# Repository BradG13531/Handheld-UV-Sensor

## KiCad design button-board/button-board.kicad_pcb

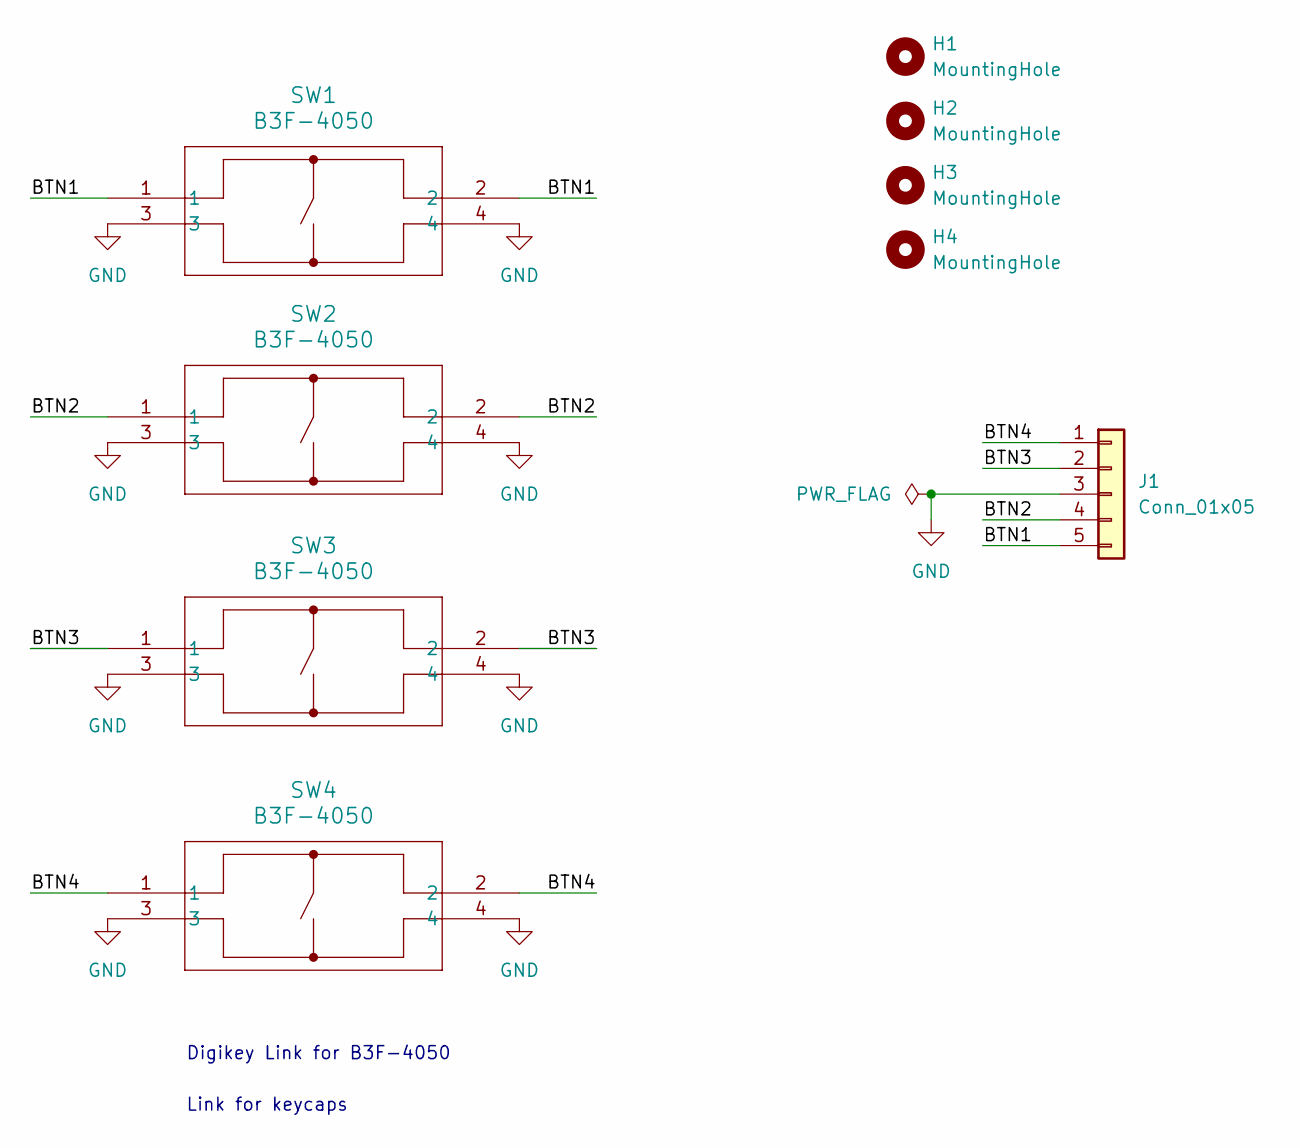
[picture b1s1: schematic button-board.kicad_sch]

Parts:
H1, H2, H3, H4: MountingHole; MountingHole_2.2mm_M2
J1: Conn_01x05; JST_PH_S5B-PH-K_1x05_P2.00mm_Horizontal
SW1, SW2, SW3, SW4: B3F-4050; SW_B3F-4050_OMR

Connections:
/BTN1: J1.5, SW1.1, SW1.2
/BTN2: J1.4, SW2.1, SW2.2
/BTN3: J1.2, SW3.1, SW3.2
/BTN4: J1.1, SW4.1, SW4.2
GND: J1.3, SW1.3, SW1.4, SW2.3, SW2.4, SW3.3, SW3.4, SW4.3, SW4.4

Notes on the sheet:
Digikey Link for B3F-4050
Link for keycaps

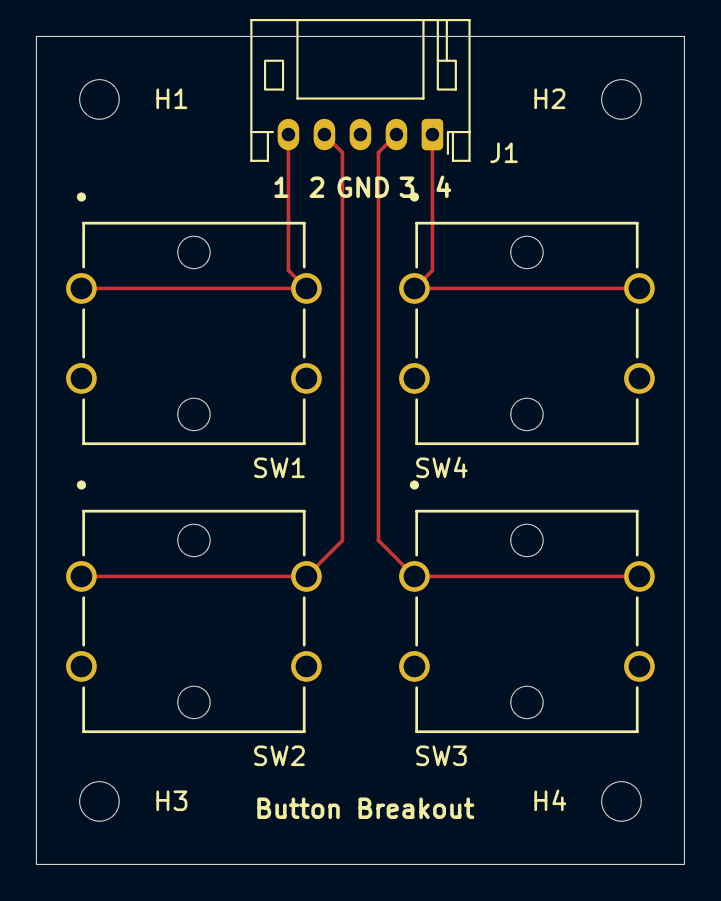
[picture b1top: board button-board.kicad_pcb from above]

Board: 2 copper layers, 36.0 x 46.0 mm, 9 parts (0 on the bottom side), 5 nets.

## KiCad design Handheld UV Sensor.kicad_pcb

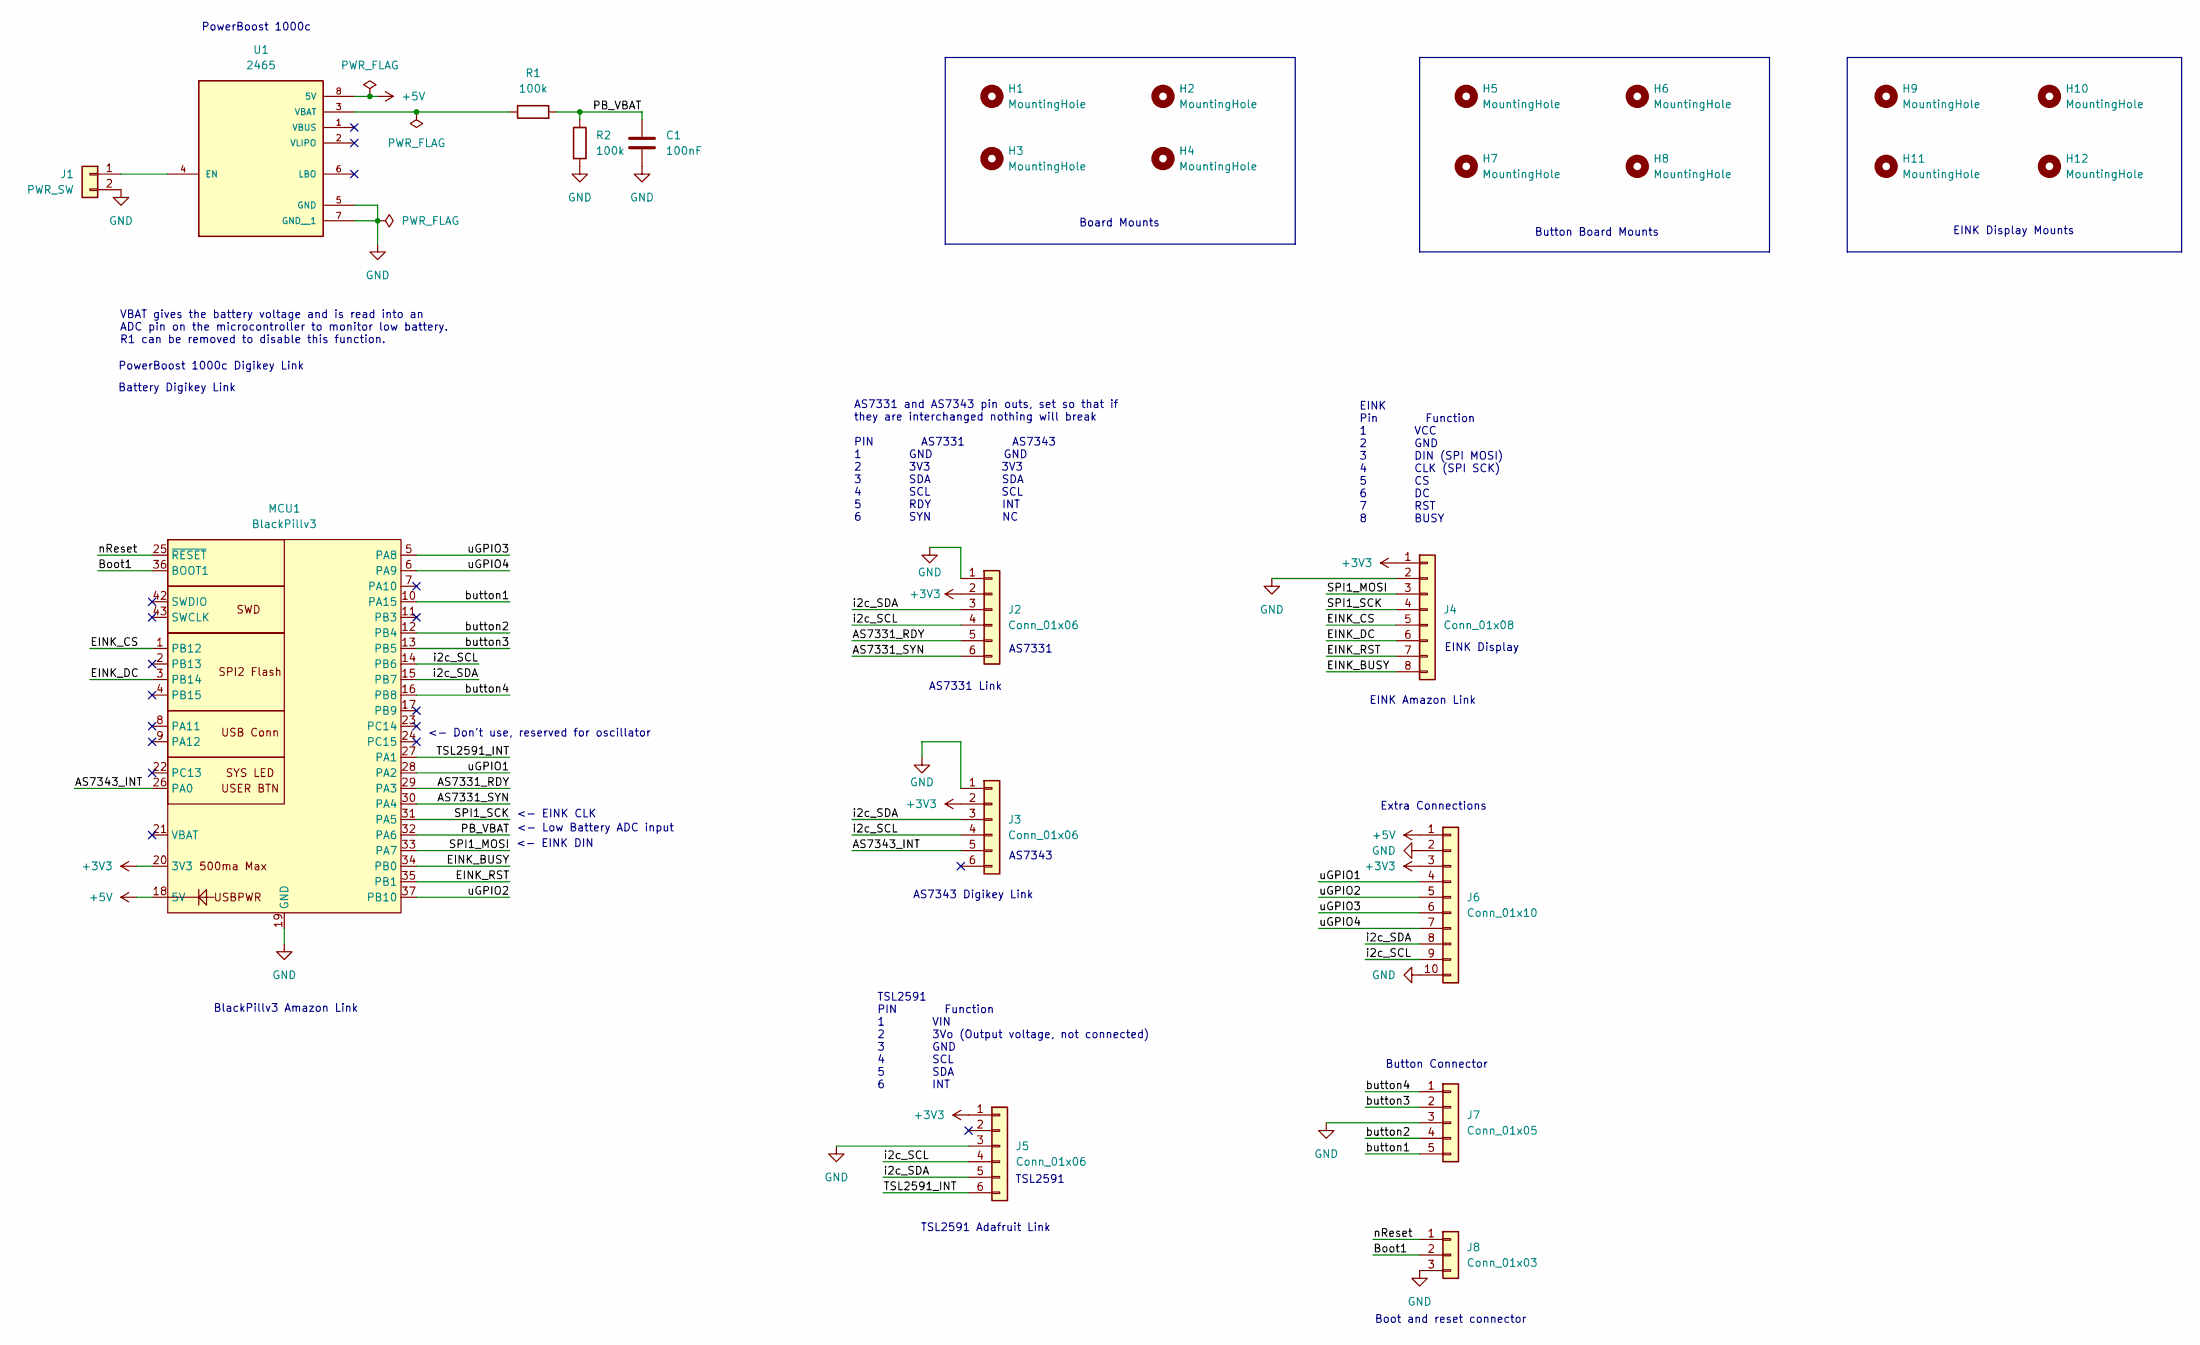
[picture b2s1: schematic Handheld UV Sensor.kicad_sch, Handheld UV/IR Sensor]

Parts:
C1: 100nF; C_0805_2012Metric_Pad1.18x1.45mm_HandSolder
H1, H2, H3, H4, H5, H6, H7, H8, H9, H10, H11, H12: MountingHole; MountingHole_2.2mm_M2
J1: PWR_SW; JST_PH_S2B-PH-K_1x02_P2.00mm_Horizontal
J2, J3, J5: Conn_01x06; JST_PH_S6B-PH-K_1x06_P2.00mm_Horizontal
J4: Conn_01x08; JST_PH_S8B-PH-K_1x08_P2.00mm_Horizontal
J6: Conn_01x10; PinHeader_1x10_P2.54mm_Vertical
J7: Conn_01x05; JST_PH_S5B-PH-K_1x05_P2.00mm_Horizontal
J8: Conn_01x03; PinHeader_1x03_P2.54mm_Vertical
MCU1: BlackPillv3; WeAct-BlackPill_DIP-40_W15.24mm-SWD
R1, R2: 100k; R_0805_2012Metric_Pad1.20x1.40mm_HandSolder
U1: 2465; MODULE_2465; PARTREV B

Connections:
+3V3: J2.2, J3.2, J4.1, J5.1, J6.3, MCU1.20 (3V3), MCU1.38 (3V3), MCU1.41 (3V3)
+5V: J6.1, MCU1.18 (5V), MCU1.40 (5V), U1.8 (5V)
/AS7331_RDY: J2.5, MCU1.29 (PA3)
/AS7331_SYN: J2.6, MCU1.30 (PA4)
/AS7343_INT: J3.5, MCU1.26 (PA0)
/Boot1: J8.2, MCU1.36 (BOOT1)
/EINK_BUSY: J4.8, MCU1.34 (PB0)
/EINK_CS: J4.5, MCU1.1 (PB12)
/EINK_DC: J4.6, MCU1.3 (PB14)
/EINK_RST: J4.7, MCU1.35 (PB1)
/PB_VBAT: C1.1, MCU1.32 (PA6), R1.2, R2.1
/SPI1_MOSI: J4.3, MCU1.33 (PA7)
/SPI1_SCK: J4.4, MCU1.31 (PA5)
/TSL2591_INT: J5.6, MCU1.27 (PA1)
/button1: J7.5, MCU1.10 (PA15)
/button2: J7.4, MCU1.12 (PB4)
/button3: J7.2, MCU1.13 (PB5)
/button4: J7.1, MCU1.16 (PB8)
/i2c_SCL: J2.4, J3.4, J5.4, J6.9, MCU1.14 (PB6)
/i2c_SDA: J2.3, J3.3, J5.5, J6.8, MCU1.15 (PB7)
/nReset: J8.1, MCU1.25 (~RESET)
/uGPIO1: J6.4, MCU1.28 (PA2)
/uGPIO2: J6.5, MCU1.37 (PB10)
/uGPIO3: J6.6, MCU1.5 (PA8)
/uGPIO4: J6.7, MCU1.6 (PA9)
GND: C1.2, J1.2, J2.1, J3.1, J4.2, J5.3, J6.2, J6.10, J7.3, J8.3, MCU1.19 (GND), MCU1.39 (GND), MCU1.44 (GND), R2.2, U1.5 (GND), U1.7 (GND__1)
unnamed: J1.1, U1.4 (EN)
unnamed: R1.1, U1.3 (VBAT)

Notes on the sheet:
EINK Display Mounts
TSL2591 Adafruit Link
EINK Pin Function 1 VCC 2 GND 3 DIN (SPI MOSI) 4 CLK (SPI SCK) 5 CS 6 DC 7 RST 8 BUSY
PowerBoost 1000c Digikey Link
Button Board Mounts
PowerBoost 1000c
Battery Digikey Link
EINK Display
Extra Connections
<- Low Battery ADC input
Button Connector
AS7343
<- Don't use, reserved for oscillator
AS7331
VBAT gives the battery voltage and is read into an ADC pin on the microcontroller to monitor low battery. R1 can be removed to disable this function.
EINK Amazon Link
<- EINK DIN
BlackPillv3 Amazon Link
AS7331 Link
TSL2591 PIN Function 1 VIN 2 3Vo (Output voltage, not connected) 3 GND 4 SCL 5 SDA 6 INT
AS7343 Digikey Link
Board Mounts
Boot and reset connector
<- EINK CLK
AS7331 and AS7343 pin outs, set so that if they are interchanged nothing will break PIN AS7331 AS7343 1 GND GND 2 3V3 3V3 3 SDA SDA 4 SCL SCL 5 RDY INT 6 SYN NC
TSL2591

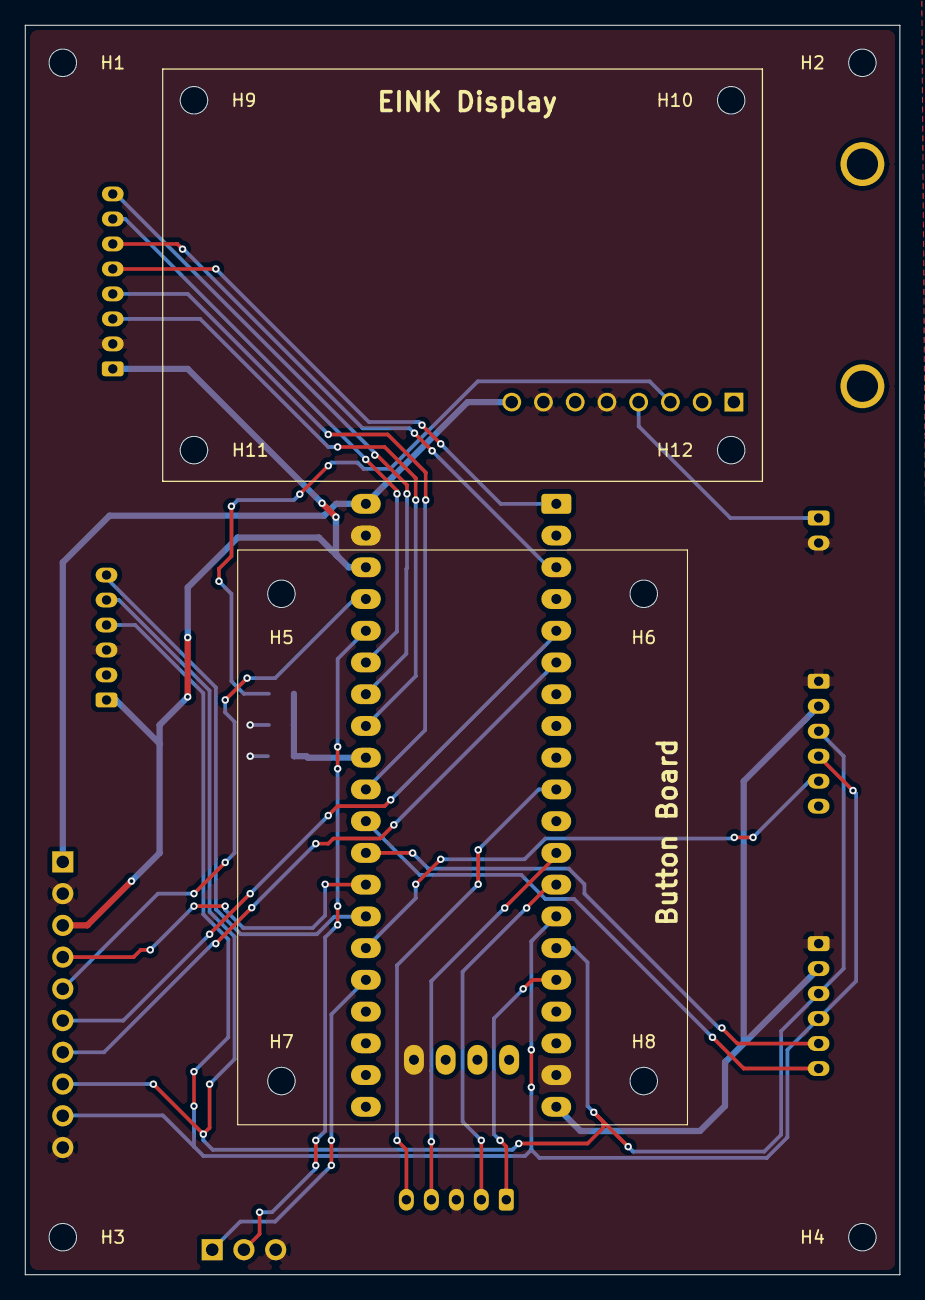
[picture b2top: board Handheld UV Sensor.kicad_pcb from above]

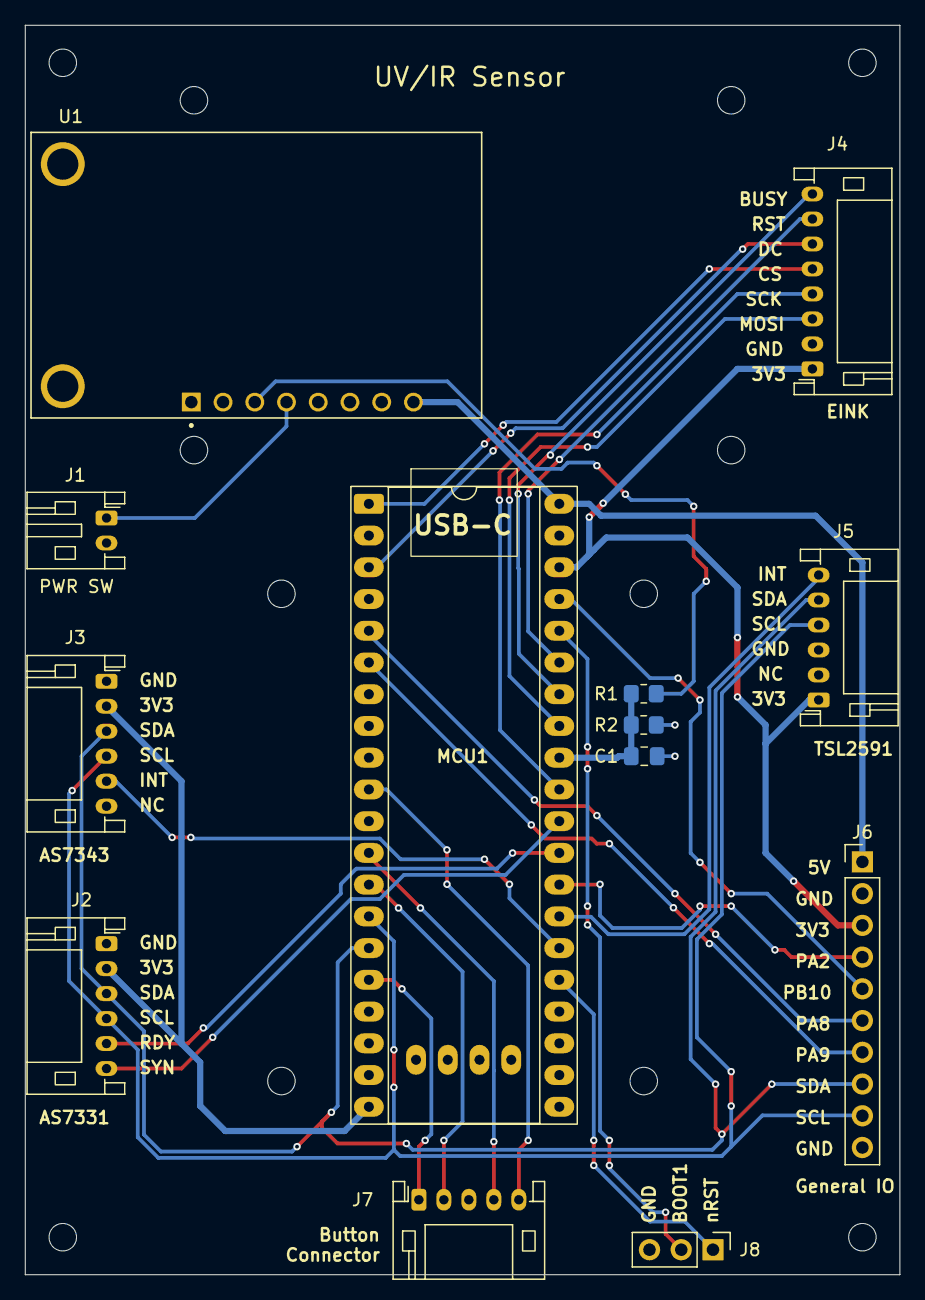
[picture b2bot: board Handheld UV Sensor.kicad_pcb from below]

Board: 2 copper layers, 70.0 x 100.0 mm, 25 parts (13 on the bottom side), 28 nets.
